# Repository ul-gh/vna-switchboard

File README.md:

# VNA-Switchboard FAN3241
KiCad project files for PCB driving a 12V...28V latching relay
from a single 5V voltage source, control is a high/low input signal.

Using an MT3608 step-up DCDC converter input current-limited
to less than 100 mA, timing and protection circuitry integrated
into FAN3241 driver IC and RF/EMC shielding provision for the
step-up coverter, this is designed for driving the direction
switch of a VNA S-parameter test set.

The input is a 6P6 western socket pinning compatible to the
DG8SAQ VNWA3. When this input is connected, no additional power
supply or control signals are required.

Schematic PDF: [VNA-Switchboard_FAN3241.pdf](VNA-Switchboard_FAN3241.pdf)

Additional instructions: Most if not all MT3608 DCDC converter boards sold
today require the following bug fix if medium output voltages are to be set:

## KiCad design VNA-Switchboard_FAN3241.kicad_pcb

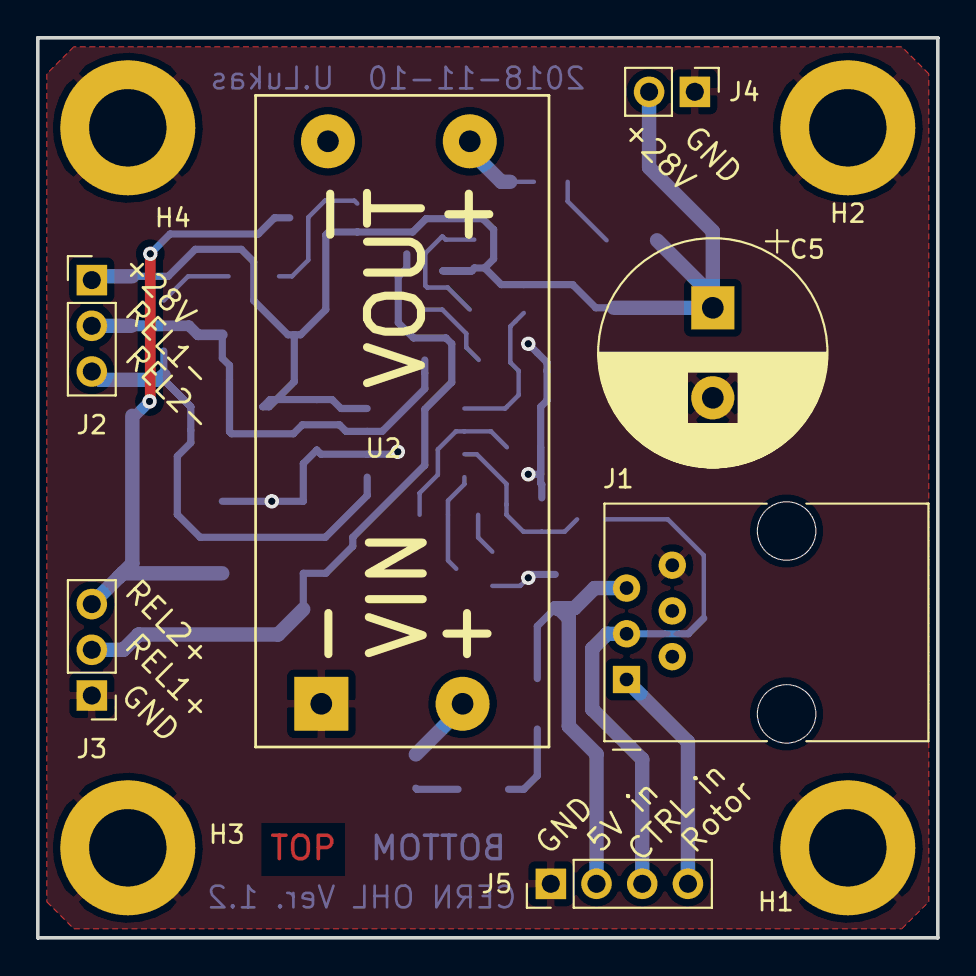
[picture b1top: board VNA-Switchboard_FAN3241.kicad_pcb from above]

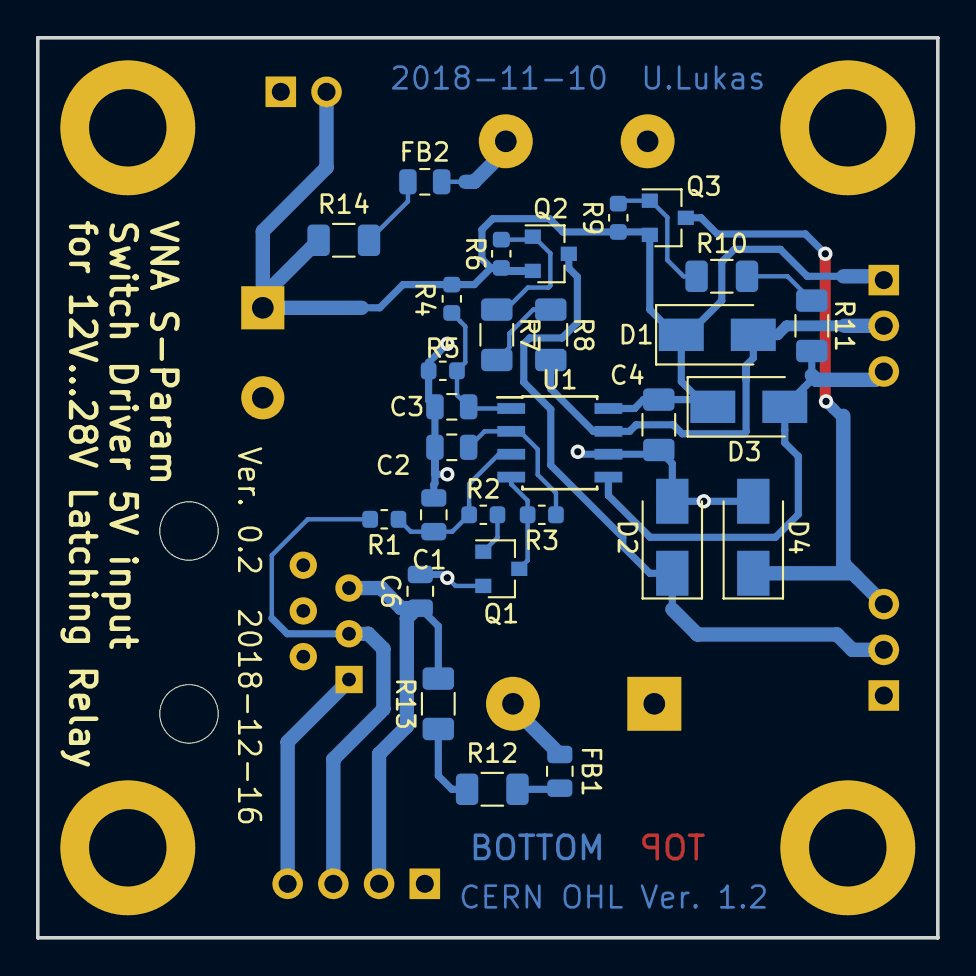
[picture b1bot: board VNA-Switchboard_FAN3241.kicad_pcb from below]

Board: 2 copper layers, 50.0 x 50.0 mm, 40 parts (29 on the bottom side), 23 nets.

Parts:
C1, C3, C6: 100n; C_0805_2012Metric
C2: 220n; C_0805_2012Metric
C4: 1µ; C_1206_3216Metric
C5: 1000µ; CP_Radial_D12.5mm_P5.00mm
D1, D2, D3, D4: S1B; D_SMA
FB1, FB2: Ferrite_Bead; L_0805_2012Metric
H1, H2, H3, H4: MountingHole_Pad; MountingHole_4.3mm_M4_DIN965_Pad
J1: 6P6C; RJ12_Amphenol_54601
J2, J3: Conn_01x03_Male; PinHeader_1x03_P2.54mm_Vertical
J4: Conn_01x02_Male; PinHeader_1x02_P2.54mm_Vertical
J5: Conn_01x04_Male; PinHeader_1x04_P2.54mm_Vertical
Q1: BC848; SOT-23
Q2, Q3: BC807; SOT-23
R1, R6, R9: 4k7; R_0603_1608Metric
R2, R4: 100k; R_0603_1608Metric
R3: 22k; R_0603_1608Metric
R5: 6k2; R_0603_1608Metric
R7, R8, R10, R11: 470; R_1206_3216Metric
R12, R13: 22; R_1206_3216Metric
R14: 100; R_1206_3216Metric
U1: FAN3241; SOIC-8_3.9x4.9mm_P1.27mm
U2: MT3608-PCB; MT3608_Step-Up_Converter_PCB

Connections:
/5V_in: C6.1, J1.5, J5.2, R13.2
/+28V: C4.1, C5.1, D1.1, D3.1, J2.1, J4.2, Q2.2, Q3.2, R4.1, R6.1, R9.1, R14.2, U1.8
/CTRL_in: J1.3, J5.3, R1.2
/Coil1_neg: D1.2, J2.2, R8.2, U1.7
/Coil1_pos: D2.1, J3.2, Q2.3
/Coil2_neg: D3.2, J2.3, R11.2, U1.5
/Coil2_pos: D4.1, J3.3, Q3.3
/Rotor: J1.1, J5.4
GND: C1.2, C2.2, C3.2, C4.2, C5.2, C6.2, D2.2, D4.2, H1.1, H2.1, H3.1, H4.1, J1.6, J3.1, J4.1, J5.1, Q1.2, R5.2, U1.6, U2.1
unnamed: C1.1, R1.1, R2.1, U1.3
unnamed: C2.1, R3.1, U1.2
unnamed: C3.1, R4.2, R5.1, U1.1
unnamed: FB1.1, R12.1
unnamed: FB1.2, U2.2
unnamed: FB2.1, R14.1
unnamed: FB2.2, U2.3
unnamed: Q1.1, R2.2
unnamed: Q1.3, R3.2, U1.4
unnamed: Q2.1, R6.2, R7.1
unnamed: Q3.1, R9.2, R10.1
unnamed: R7.2, R8.1
unnamed: R10.2, R11.1
unnamed: R12.2, R13.1

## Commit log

2018-11-10 Initial Version 0.1
2018-11-10 Added readme and license text
2018-11-10 Added preview image
2018-11-10 Added PDF schematic and top side preview image
2018-11-10 link fixed
2018-11-11 Default view changed
2018-12-16 R4 and R5 wrong value. C5 larger value optinal.
2019-01-03 Added image and description
2019-01-03 Added image showing MT3608 DCDC converter bug fix

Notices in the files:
VNA-Switchboard_FAN3241.kicad_pcb:
CERN OHL Ver. 1.2
